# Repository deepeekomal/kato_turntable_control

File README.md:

# kato_turntable_control
Files for the control of Kato N Scale Turntable 20-283.
Detais are on ntrains.org https://www.ntrains.org/katoturntabledccver2/

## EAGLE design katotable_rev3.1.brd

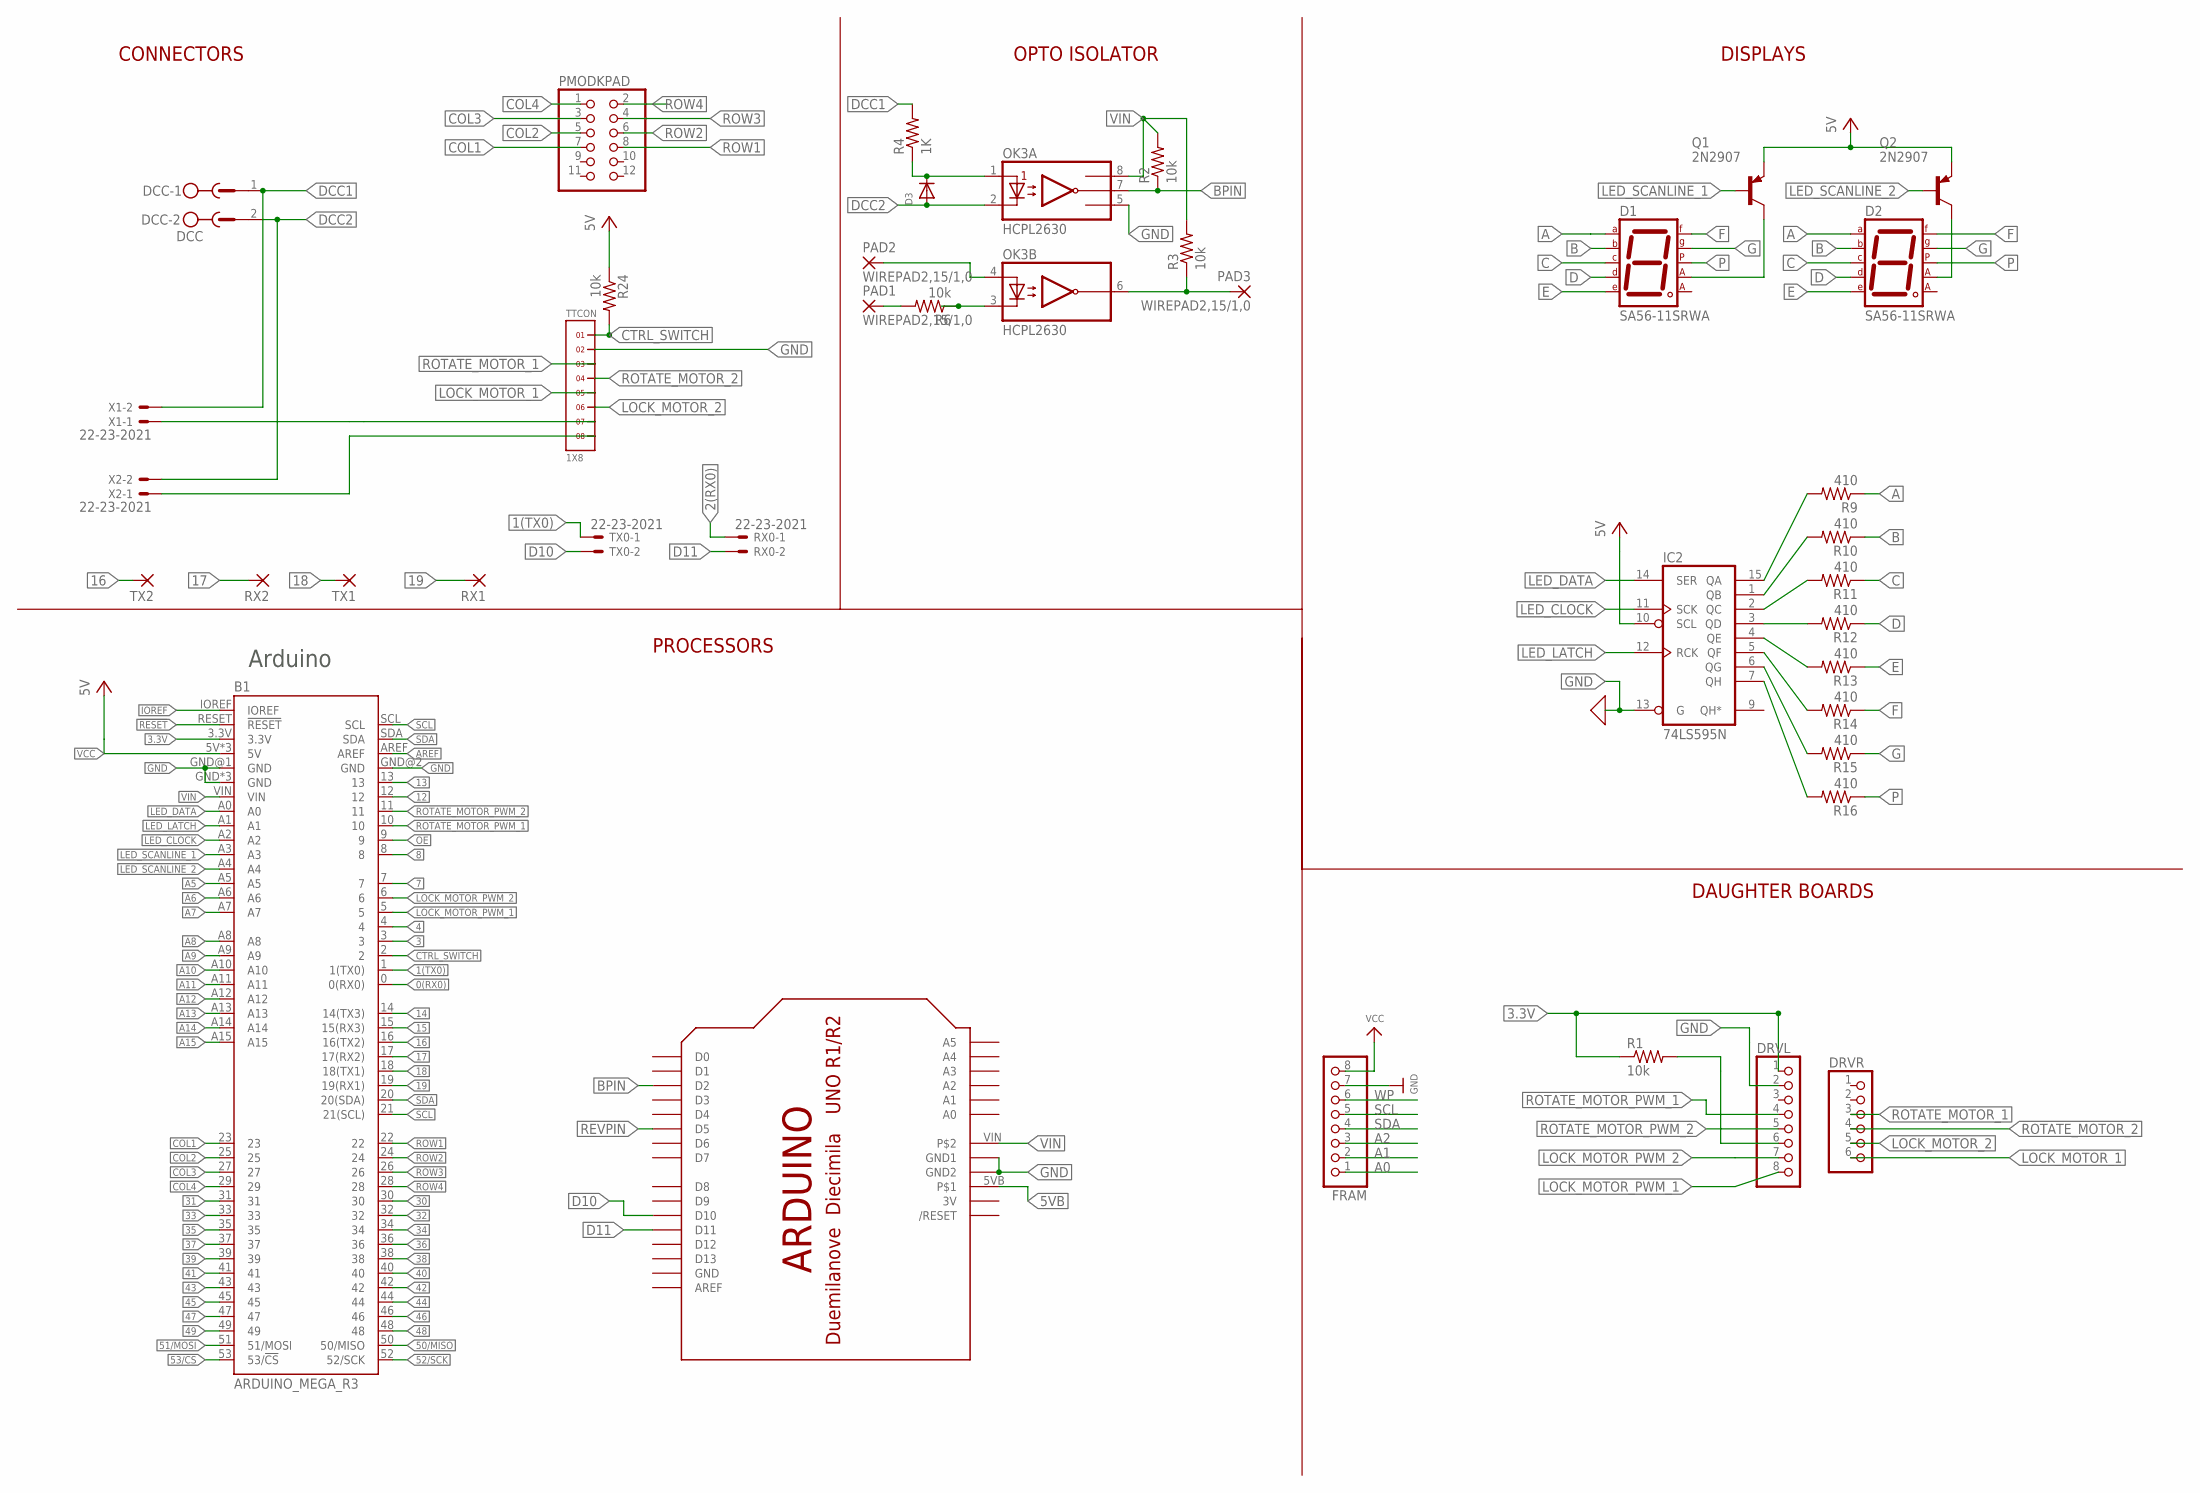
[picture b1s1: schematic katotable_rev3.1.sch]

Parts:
B1: ARDUINO_MEGA_R3; ARDUINO_MEGA_NO_SILK
D1, D2: SA56-11SRWA; 7SEG-13
D3: DIODEDO-1N4148; DO-1N4148
DCC: DCC; MSTBV2
DECODER: ARDUINO-BPLACE
DRVL: PINHD-1X8; 1X08
DRVR: PINHD-1X6; 1X06
FRAM: HEADER-1X870MIL; 1X08_ROUND_70
IC2: 74LS595N; DIL16
OK3: HCPL2630; DIL08
PAD1, PAD2, PAD3: WIREPAD2,15/1,0; 2,15/1,0
PMODKPAD: PINHD-2X6/90; 2X06/90
Q1, Q2: 2N2907; TO18
R1, R2, R3, R6, R24: 10k; 0204/7
R4: 1K; 0207/10
R9, R10, R11, R12, R13, R14, R15, R16: 410; 0204/7
RX0: 22-23-2021
RX1, RX2: WIREPAD2,54/1,0; 2,54/1,0
TTCON: 1X8
TX0: 22-23-2021
TX1, TX2: WIREPAD2,54/1,0; 2,54/1,0
X1, X2: 22-23-2021

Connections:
0(RX0): B1.0 (0(RX0))
1(TX0): B1.1 (1(TX0)), TX0.1
2(RX0): RX0.1
3: B1.3
3.3V: B1.3.3V, DRVL.1, R1.1
3V: DECODER.3V
4: B1.4
5VB: DECODER.5VB
7: B1.7
8: B1.8
12: B1.12
13: B1.13
14: B1.14 (14(TX3))
15: B1.15 (15(RX3))
16: B1.16 (16(TX2)), TX2.1
17: B1.17 (17(RX2)), RX2.1
18: B1.18 (18(TX1)), TX1.1
19: B1.19 (19(RX1)), RX1.1
30: B1.30
31: B1.31
32: B1.32
33: B1.33
34: B1.34
35: B1.35
36: B1.36
37: B1.37
38: B1.38
39: B1.39
40: B1.40
41: B1.41
42: B1.42
43: B1.43
44: B1.44
45: B1.45
46: B1.46
47: B1.47
48: B1.48
49: B1.49
50/MISO: B1.50 (50/MISO)
51/MOSI: B1.51 (51/MOSI)
52/SCK: B1.52 (52/SCK)
53/!CS: B1.53 (53/!CS)
!RESET: B1.RESET (!RESET)
A: D1.7 (A), D2.7 (A), R9.1
A0: FRAM.1
A1: FRAM.2
A2: FRAM.3
A5: B1.A5
A6: B1.A6
A7: B1.A7
A8: B1.A8
A9: B1.A9
A10: B1.A10
A11: B1.A11
A12: B1.A12
A13: B1.A13
A14: B1.A14
A15: B1.A15
AREF: B1.AREF
B: D1.6 (B), D2.6 (B), R10.1
BPIN: DECODER.D2, OK3.7 (VO1), R2.1
C: D1.4 (C), D2.4 (C), R11.1
COL1: B1.23, PMODKPAD.7
COL2: B1.25, PMODKPAD.5
COL3: B1.27, PMODKPAD.3
COL4: B1.29, PMODKPAD.1
COM: OK3.4 (A2), PAD2.1
CTRL_SWITCH: B1.2, R24.2, TTCON.1
D: D1.2 (D), D2.2 (D), R12.1
D10: DECODER.D10, TX0.2
D11: DECODER.D11, RX0.2
DCC1: DCC.1, R4.2, X1.2
DCC2: D3.A, DCC.2, OK3.2 (C1), X2.2
E: D1.1 (E), D2.1 (E), R13.1
F: D1.9 (F), D2.9 (F), R14.1
G: D1.10 (G), D2.10 (G), R15.1
GND: B1.GND, B1.GND@1 (GND), B1.GND@2 (GND), B1.GND@3 (GND), B1.GND@4 (GND), DECODER.GND, DECODER.GND1, DECODER.GND2, DRVL.2, FRAM.7, IC2.8 (GND), IC2.13 (G), OK3.5 (GND), TTCON.2
IOREF: B1.IOREF
LED_CLOCK: B1.A2, IC2.11 (SCK)
LED_DATA: B1.A0, IC2.14 (SER)
LED_LATCH: B1.A1, IC2.12 (RCK)
LED_SCANLINE_1: B1.A3, Q1.2 (B)
LED_SCANLINE_2: B1.A4, Q2.2 (B)
LOCK_MOTOR_1: DRVR.6, TTCON.5
LOCK_MOTOR_2: DRVR.5, TTCON.6
LOCK_MOTOR_PWM_1: B1.5, DRVL.8
LOCK_MOTOR_PWM_2: B1.6, DRVL.7
unnamed: D3.C, OK3.1 (A1), R4.1
unnamed: DRVL.6, R1.2
unnamed: PAD1.1, R6.2
unnamed: OK3.3 (C2), R6.1
unnamed: TTCON.7, X1.1
unnamed: TTCON.8, X2.1
unnamed: IC2.15 (QA), R9.2
unnamed: IC2.1 (QB), R10.2
unnamed: IC2.2 (QC), R11.2
unnamed: IC2.3 (QD), R12.2
unnamed: IC2.4 (QE), R13.2
unnamed: IC2.5 (QF), R14.2
unnamed: IC2.6 (QG), R15.2
unnamed: IC2.7 (QH), R16.2
unnamed: D1.3 (CA1), Q1.3 (C)
unnamed: D2.3 (CA1), Q2.3 (C)
OE: B1.9
P: D1.5 (DP), D2.5 (DP), R16.1
REVPIN: DECODER.D5, OK3.6 (VO2), PAD3.1, R3.1
ROTATE_MOTOR_1: DRVR.3, TTCON.3
ROTATE_MOTOR_2: DRVR.4, TTCON.4
ROTATE_MOTOR_PWM_1: B1.10, DRVL.4
ROTATE_MOTOR_PWM_2: B1.11, DRVL.5
ROW1: B1.22, PMODKPAD.8
ROW2: B1.24, PMODKPAD.6
ROW3: B1.26, PMODKPAD.4
ROW4: B1.28, PMODKPAD.2
SCL: B1.21 (21(SCL)), B1.SCL, FRAM.5
SDA: B1.20 (20(SDA)), B1.SDA, FRAM.4
VCC: B1.5V, B1.5V@1 (5V), B1.5V@2 (5V), FRAM.8, IC2.10 (SCL), IC2.16 (VCC), Q1.1 (E), Q2.1 (E), R24.1
VIN: B1.VIN, DECODER.VIN, OK3.8 (VCC), R2.2, R3.2
WP: FRAM.6

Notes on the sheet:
Arduino
CONNECTORS
OPTO ISOLATOR
DISPLAYS
PROCESSORS
DAUGHTER BOARDS

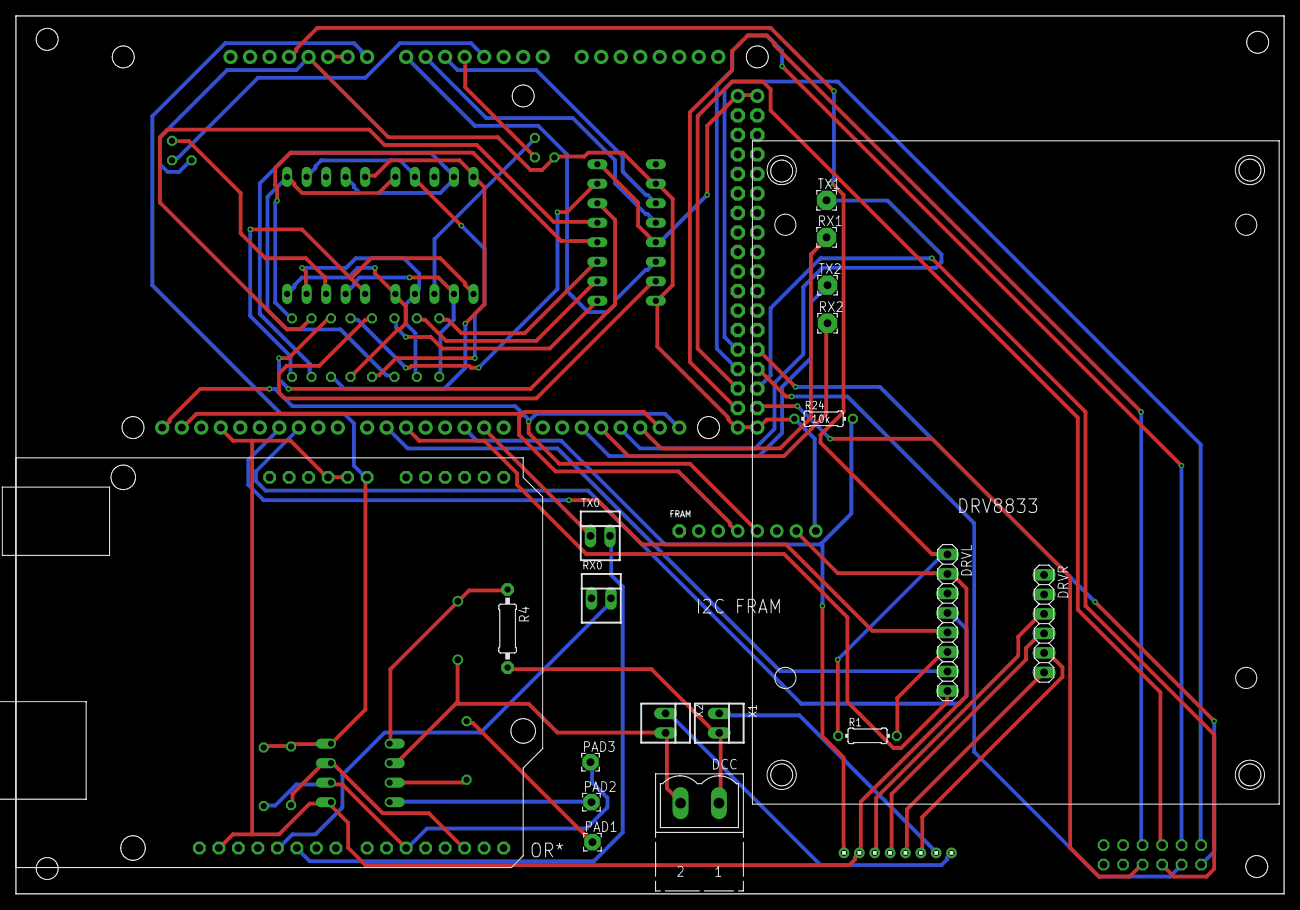
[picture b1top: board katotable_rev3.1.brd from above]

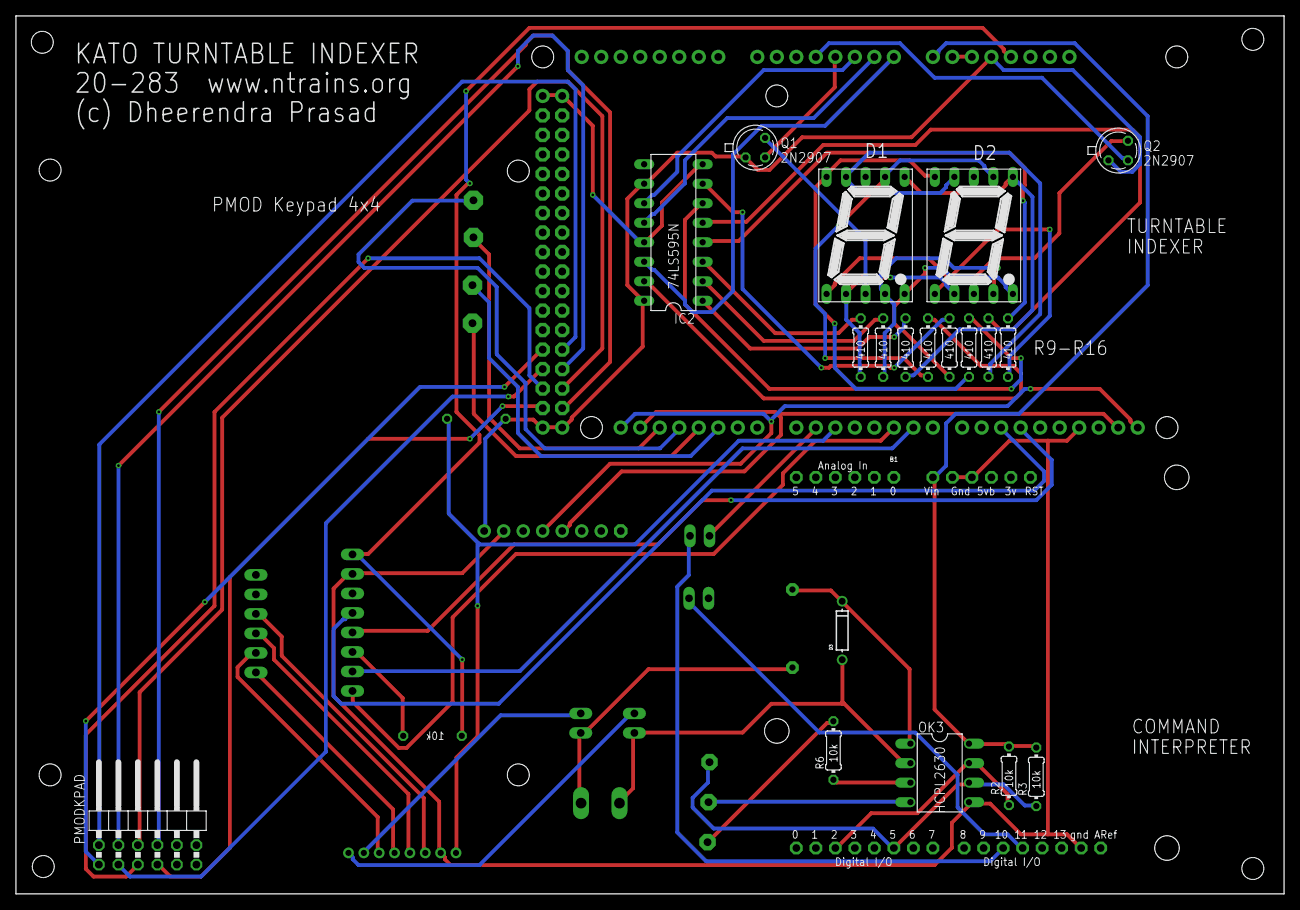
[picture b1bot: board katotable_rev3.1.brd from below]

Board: 2 copper layers, 165.1 x 114.3 mm, 40 parts (21 on the bottom side), 64 nets.

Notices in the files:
parts and their libraries:
SparkFun-Boards: Licensing: Creative Commons ShareAlike 4.0 International - https://creativecommons.org/licenses/by-sa/4.0
microbuilder: This work is placed in the public domain, and may be freely used for commercial and non-commercial work with the following conditions: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
